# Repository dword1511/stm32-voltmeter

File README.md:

# STM32-based Voltage Meter Firmware for Multiple Hardware Platforms

This repository contains firmware for STM32 MCU-based voltage meters,
which can be easily expanded to different hardware platforms.

## General Build Instructions

You will need the following packages (Debian/Ubuntu):

* build-essential
* gcc-arm-none-eabi
* git
* dialog

Depending on how you will program the firmware into the MCU, you will need:

* openocd
* stlink-tools
* dfu-util
* gdb-multiarch

This project uses `libopencm3`. It will be automatically checked out during the building process.
To build the firmware, run `make select` to select a target board, then type `make`.
To flash it, connect the board to a debugger, or UART (for ISP), or USB (for DFU), and then run `make flash`.
For ISP/DFU, remember to set BOOT0 (and BOOT1 if available) on the boards properly.

Under the `boards` folder there are Makefiles for each target board.
These files determine how the master Makefile will flash the MCU.

## Special Information for the CPT Field Probe

These probes are compact battery-powered voltage meters designed to
measure wireless power transfer at microwatt- to sub-watt-level (depending on the load).
Their form factor reduces stray coupling and falsely high readings.
The probe also reserved space for a full-/half-wave rectifier,
an adjustable load, and the CPT RX matching network.
The voltage measurement can be trimmed and calibrated against an accurate instrument.
The maximum input voltage is around 50 V with the 2M/100k resistive divider,
depending on the load, filtering capacitor rating, and the battery voltage
(as the VDDA is connected to battery without LDO -- the VDDA is calibrated against STM32's internal bandgap).

The average current consumption of these probes is under 150 microampere (see `boards/cpt-fieldprobe.md`).
A typical CR2032 battery has around 220 mAh, thus one battery can support 2 months of continuous, uninterrupted operation.

The hardware design files are located in `pcb/cpt-fieldprobe`.
To flash the probe, connect a SWD debugger (ST-Link) to the test points on the back of the PCB via enameled wires.

The probe was part of the following work. Please kindly consider citing the paper as shown if you find it useful:

```
@inproceedings{Capttery,
 author = {Zhang, Chi and Kumar, Sidharth and Bharadia, Dinesh},
 title = {{Capttery: Scalable Battery-like Room-level Wireless Power}},
 booktitle = {Proc. of ACM MobiSys},
 year = {2019},
}
```

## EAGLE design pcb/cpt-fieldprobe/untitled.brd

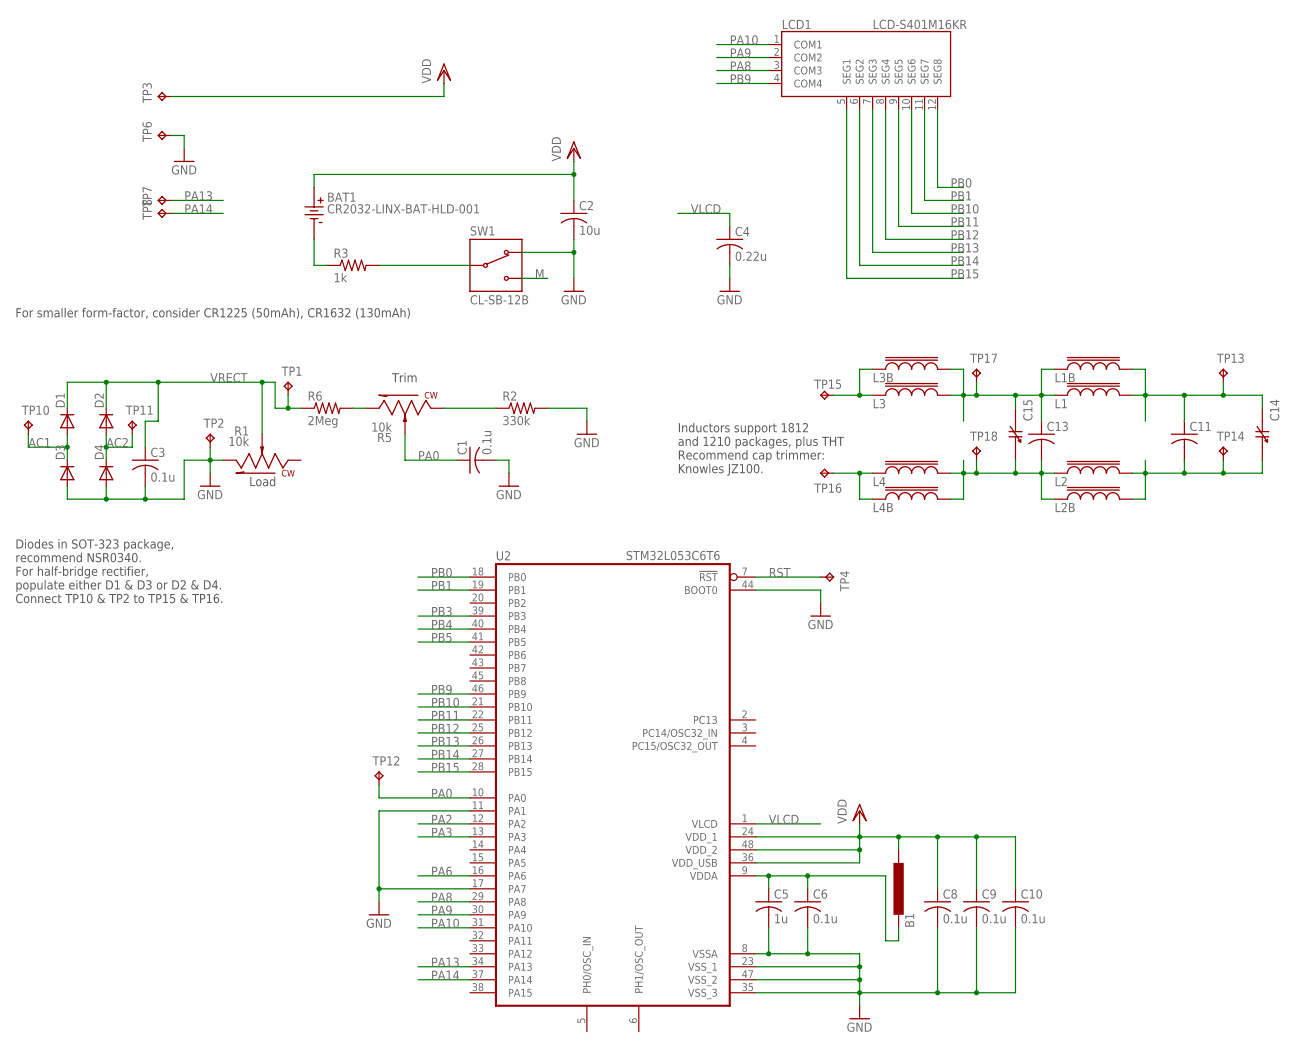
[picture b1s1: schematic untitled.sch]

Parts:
B1: BEAD-0603; 0603
BAT1: CR2032-LINX-BAT-HLD-001; LINX-BAT-HLD-001
C1, C3, C6, C8, C9, C10: 0.1u; C0402
C2: 10u; C0603
C4: 0.22u; C0402
C5: 1u; C0603
C11: 47p; C0805
C13: 82p; C0805
C14, C15: 30p; SGC3
D1, D2, D3, D4: DIODE-SOD523; SOD523
L1, L2: 100u; 1812
L1B, L2B, L3B, L4B: INDUCTOR-1210; 1210
L3, L4: 68u; 1812
LCD1: LCD-S401M16KR; LCD-S401M16K
R1: 10k; BOURNS-3296W
R2: 330k; R0402
R3: 1k; R0402
R5: 10k; TC33X
R6: 2Meg; R0603
SW1: CL-SB-12B
TP1, TP2, TP10, TP11, TP13, TP14, TP15, TP16, TP17, TP18: TPPAD1-13; P1-13
TP3, TP4, TP6, TP7, TP8, TP12: TPB1,27; B1,27
U2: STM32L053C6T6; QFP-48-7X7

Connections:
AC1: D1.A, D3.C, TP10.TP
AC2: D2.A, D4.C, TP11.TP
GND: C1.2, C2.2, C3.2, C4.2, C5.2, C6.2, C8.2, C9.2, C10.2, D3.A, D4.A, R1.3 (CW), R2.2, SW1.P$1 (A), TP2.TP, TP6.TP, U2.8 (VSSA), U2.11 (PA1), U2.17 (PA7), U2.23 (VSS_1), U2.35 (VSS_3), U2.44 (BOOT0), U2.47 (VSS_2)
M: SW1.P$2 (B)
unnamed: C11.2, C14.2 (B), L2.2, L2B.2, TP14.TP
unnamed: C11.1, C14.1 (A), L1.2, L1B.2, TP13.TP
unnamed: C13.1, C15.1 (A), L1.1, L1B.1, L3.2, L3B.2, TP17.TP
unnamed: B1.1, C5.1, C6.1, U2.9 (VDDA)
unnamed: R5.3 (CW), R6.2
unnamed: R2.1, R5.1 (CCW)
unnamed: R3.2, SW1.COM$1 (COM)
unnamed: C13.2, C15.2 (B), L2.1, L2B.1, L4.2, L4B.2, TP18.TP
unnamed: L3.1, L3B.1, TP15.TP
unnamed: BAT1.BAT-, R3.1
unnamed: L4.1, L4B.1, TP16.TP
PA0: C1.1, R5.2 (W), TP12.TP, U2.10 (PA0)
PA2: U2.12 (PA2)
PA3: U2.13 (PA3)
PA6: U2.16 (PA6)
PA8: LCD1.3 (COM3), U2.29 (PA8)
PA9: LCD1.2 (COM2), U2.30 (PA9)
PA10: LCD1.1 (COM1), U2.31 (PA10)
PA13: TP7.TP, U2.34 (PA13)
PA14: TP8.TP, U2.37 (PA14)
PB0: LCD1.12 (SEG8), U2.18 (PB0)
PB1: LCD1.11 (SEG7), U2.19 (PB1)
PB3: U2.39 (PB3)
PB4: U2.40 (PB4)
PB5: U2.41 (PB5)
PB9: LCD1.4 (COM4), U2.46 (PB9)
PB10: LCD1.10 (SEG6), U2.21 (PB10)
PB11: LCD1.9 (SEG5), U2.22 (PB11)
PB12: LCD1.8 (SEG4), U2.25 (PB12)
PB13: LCD1.7 (SEG3), U2.26 (PB13)
PB14: LCD1.6 (SEG2), U2.27 (PB14)
PB15: LCD1.5 (SEG1), U2.28 (PB15)
RST: TP4.TP, U2.7 (!RST!)
VDD: B1.2, BAT1.BAT+1 (BAT+), BAT1.BAT+2 (BAT+), C2.1, C8.1, C9.1, C10.1, TP3.TP, U2.24 (VDD_1), U2.36 (VDD_USB), U2.48 (VDD_2)
VLCD: C4.1, U2.1 (VLCD)
VRECT: C3.1, D1.C, D2.C, R1.2 (W), R6.1, TP1.TP

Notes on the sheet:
For smaller form-factor, consider CR1225 (50mAh), CR1632 (130mAh)
Inductors support 1812 and 1210 packages, plus THT Recommend cap trimmer: Knowles JZ100.
Load
Trim
Diodes in SOT-323 package, recommend NSR0340. For half-bridge rectifier, populate either D1 & D3 or D2 & D4. Connect TP10 & TP2 to TP15 & TP16.

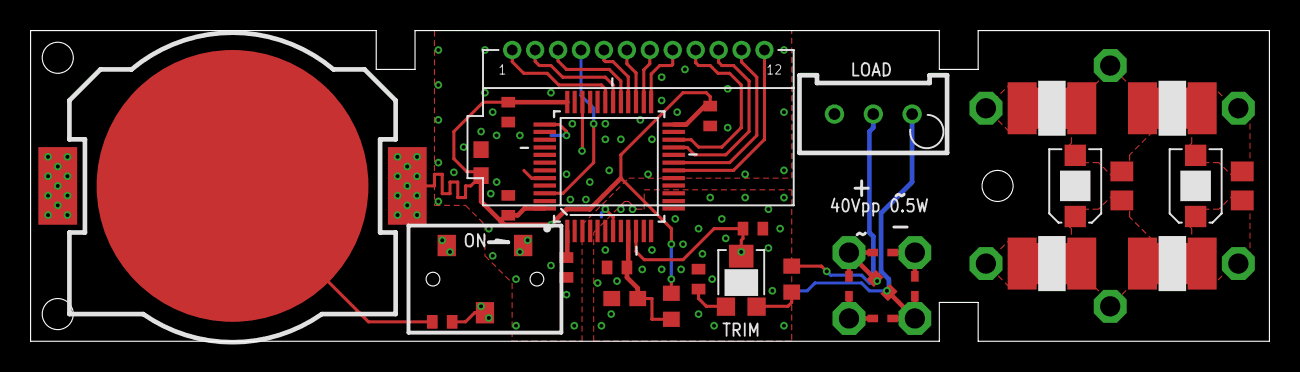
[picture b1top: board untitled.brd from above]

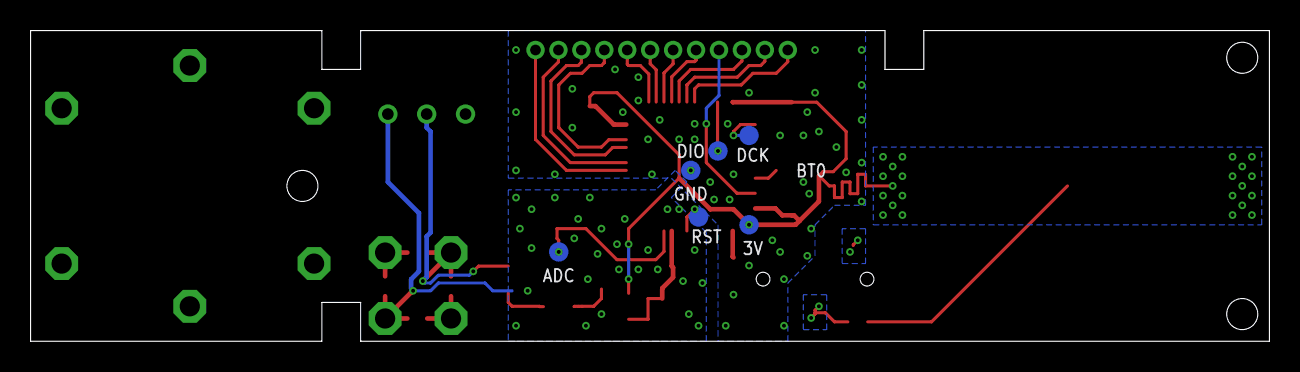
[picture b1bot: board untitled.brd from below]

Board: 2 copper layers, 81.0 x 20.3 mm, 51 parts (6 on the bottom side), 33 nets.

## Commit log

2018-09-21 skeleton ready
2018-09-21 done testing disp
2018-10-03 prepare for multi-target support, wip, nothing works yet
2018-10-03 bugfixes
2018-10-05 fix clock
2018-10-13 add multiple flash target
2018-10-14 add tick_delay and led duty cycle
2018-10-15 fixes
2018-10-15 first fully functional version
2018-10-15 fix comment
2018-10-15 small fixes
2018-10-15 start working on l0
2018-10-16 fxied lcd, adc not working
2018-10-17 generalize and fix l0 adc
2018-10-17 grand refactor
2018-10-17 minor adj and doc
2019-01-19 long overdue update
2019-07-28 add pcb files
2019-08-01 documentation
2019-08-01 add license
2019-08-01 add readme
